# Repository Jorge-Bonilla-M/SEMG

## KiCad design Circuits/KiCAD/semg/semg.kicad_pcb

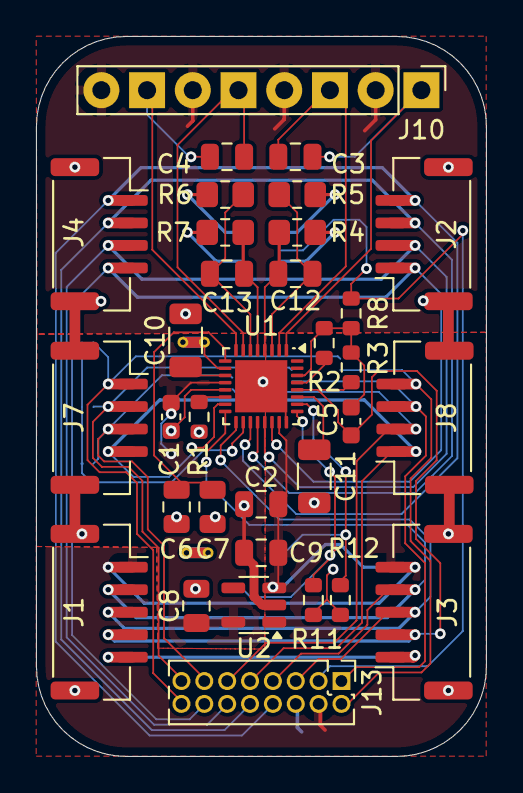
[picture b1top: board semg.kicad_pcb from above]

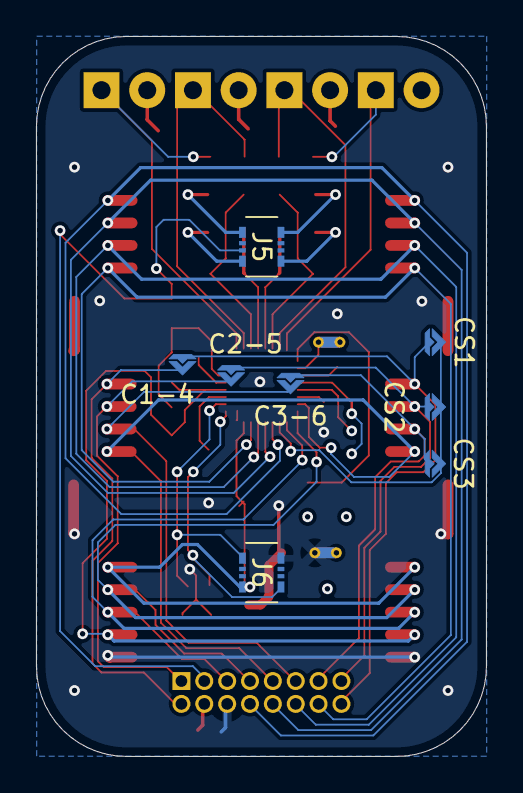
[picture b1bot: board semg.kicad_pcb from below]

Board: 4 copper layers, 25.0 x 40.0 mm, 43 parts (8 on the bottom side), 41 nets.

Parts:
C1: 100nF; C_0603_1608Metric
C1-4, C2-5, C3-6: SolderJumper_2_Open; JumperDiamond
C2, C7: 100nF; C_0805_2012Metric
C3, C4, C12, C13: 4.7nF; C_0805_2012Metric
C5: 1.5nF; C_0603_1608Metric
C6: 22uF; C_0805_2012Metric
C8, C9: 1uF; C_0805_2012Metric
C10, C11: 2.2uF; C_1206_3216Metric
CS1, CS2, CS3: SolderJumper_2_Open; JumperDiamond
J1, J3: Miscelaneous; JST_GH_SM05B-GHS-TB_1x05-1MP_P1.25mm_Horizontal
J2, J4: SPI; JST_GH_SM04B-GHS-TB_1x04-1MP_P1.25mm_Horizontal
J5, J6: 505006-0812; 5050060812
J7, J8: CS_SPI; JST_GH_SM04B-GHS-TB_1x04-1MP_P1.25mm_Horizontal
J10: Conn_01x08_Pin; PinHeader_1x08_P2.54mm_Vertical
J13: Conn_02x08_Odd_Even; PinHeader_2x08_P1.27mm_Vertical
NT1, NT2: NetTie_2; NetTie-2_THT_Pad0.3mm
R1: 1k; R_0603_1608Metric
R2, R8: 100k; R_0603_1608Metric
R3: 1M; R_0603_1608Metric
R4, R5, R6, R7: 4.7k; R_0805_2012Metric_Pad1.20x1.40mm_HandSolder
R11, R12: 10k; R_0603_1608Metric
U1: ADS1292IRSMR; QFN-32-1EP_4x4mm_P0.4mm_EP2.9x2.9mm
U2: AP2112K-3.3; SOT-23-5

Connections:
+3.3V: C2.1, C9.2, J1.1, J3.5, J6.P2, J13.4, U1.23 (DVDD), U2.1 (VIN), U2.3 (EN)
+3.3VA: C1.1, C8.2, U1.12 (AVDD), U2.5 (VOUT)
CLK: J1.3, J3.3, J13.5, U1.17 (CLK)
CS: CS1.2 (B), CS2.2 (B), CS3.2 (B), U1.18 (~CS)
CS1: C1-4.1 (A), CS1.1 (A), J7.1, J13.16
CS2: C2-5.1 (A), CS2.1 (A), J7.2, J13.15
CS3: C3-6.1 (A), CS3.1 (A), J7.3, J13.13
CS4: C1-4.2 (B), J8.4, J13.2
CS5: C2-5.2 (B), J8.3, J13.1
CS6: C3-6.2 (B), J8.2, J13.11
DRDY: J2.1, J4.4, J13.14, U1.22 (~DRDY)
GND: C2.2, C9.1, C10.2, C11.2, J1.5, J1.MP (Pin_6), J2.MP (Pin_5), J3.1, J3.MP (Pin_6), J4.MP (Pin_5), J6.P3, J7.MP (Pin_5), J8.MP (Pin_5), J13.6, NT1.1, R1.2, R11.2, R12.2, U1.24 (DGND), U1.33 (EXP), U2.2 (GND)
GNDA: C1.2, C6.2, C7.2, C8.1, J10.2, J10.4, J10.6, J10.8, NT1.2, NT2.2, U1.13 (AVSS)
GPIO1: J6.P4, R12.1, U1.26 (GPIO1/RCLK1)
GPIO2: J6.P1, R11.1, U1.25 (GPIO2/RCLK2)
IN1N: C12.2, R5.2, U1.3 (IN1N)
IN1N_: J5.P4, R5.1
IN1P: C12.1, R4.2, U1.4 (IN1P)
IN1P_: J5.P2, R4.1
IN2N: C13.2, R7.2, U1.5 (IN2N)
IN2N_: J5.P1, R7.1
IN2P: C13.1, R6.2, U1.6 (IN2P)
IN2P_: J5.P3, R6.1
MISO: J2.2, J4.3, J13.12, U1.21 (DOUT)
MOSI: J2.4, J4.1, J13.8, U1.19 (DIN)
unnamed: R1.1, U1.14 (CLKSEL)
unnamed: C10.1, U1.11 (VCAP1)
unnamed: C11.1, U1.27 (VCAP2)
PGA1N: C3.1, J10.1, U1.1 (PGA1N)
PGA1P: C3.2, J10.3, U1.2 (PGA1P)
PGA2N: C4.1, J10.5, U1.7 (PGA2N)
PGA2P: C4.2, J10.7, U1.8 (PGA2P)
PWDN: J7.4, J8.1, J13.9, U1.15 (~PWDN/RST)
RLD: J5.S2, J13.3, R8.2
RLDIN: R2.2, U1.29 (RLDIN/RLDREF)
RLDINV: C5.1, J1.4, J3.2, R3.2, U1.28 (RLDINV)
RLDOUT: C5.2, R2.1, R3.1, R8.1, U1.30 (RLDOUT)
SPICLK: J2.3, J4.2, J13.10, U1.20 (SCLK)
START: J1.2, J3.4, J13.7, U1.16 (START)
VREFN: NT2.1, U1.10 (VREFN)
VREFP: C6.1, C7.1, U1.9 (VREFP)

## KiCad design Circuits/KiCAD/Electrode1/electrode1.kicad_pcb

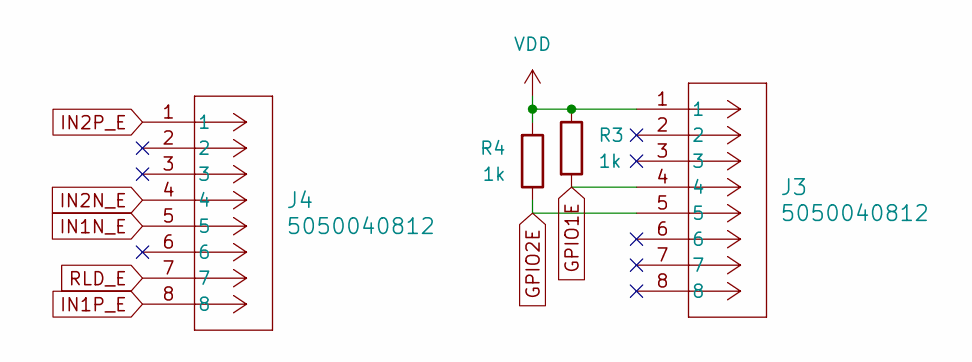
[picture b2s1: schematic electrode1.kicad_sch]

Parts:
J3, J4: 5050040812; CONN8_505004-0812_MOL
R3, R4: 1k; C_0805_2012Metric

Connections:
GPIO1E: J3.4, R3.2
GPIO2E: J3.5, R4.1
IN1N_E: J4.5
IN1P_E: J4.8
IN2N_E: J4.4
IN2P_E: J4.1
RLD_E: J4.7
VDD: J3.1, R3.1, R4.2

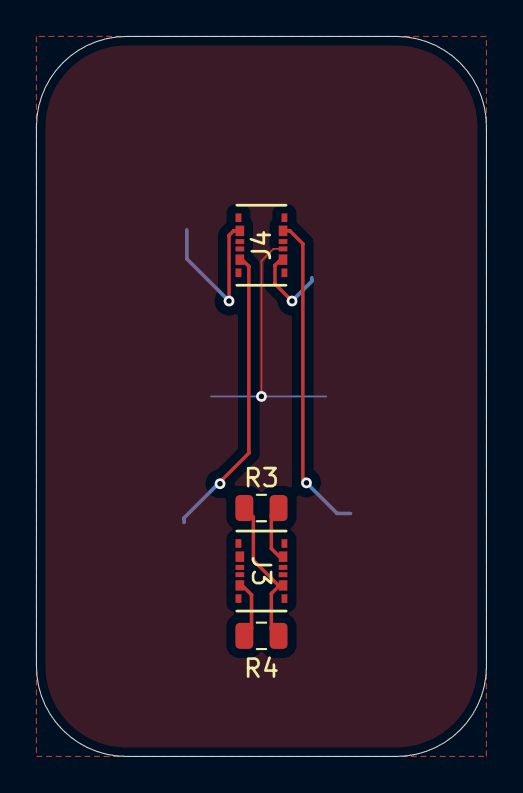
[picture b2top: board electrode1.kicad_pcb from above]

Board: 2 copper layers, 25.0 x 40.0 mm, 4 parts (0 on the bottom side), 3 nets.

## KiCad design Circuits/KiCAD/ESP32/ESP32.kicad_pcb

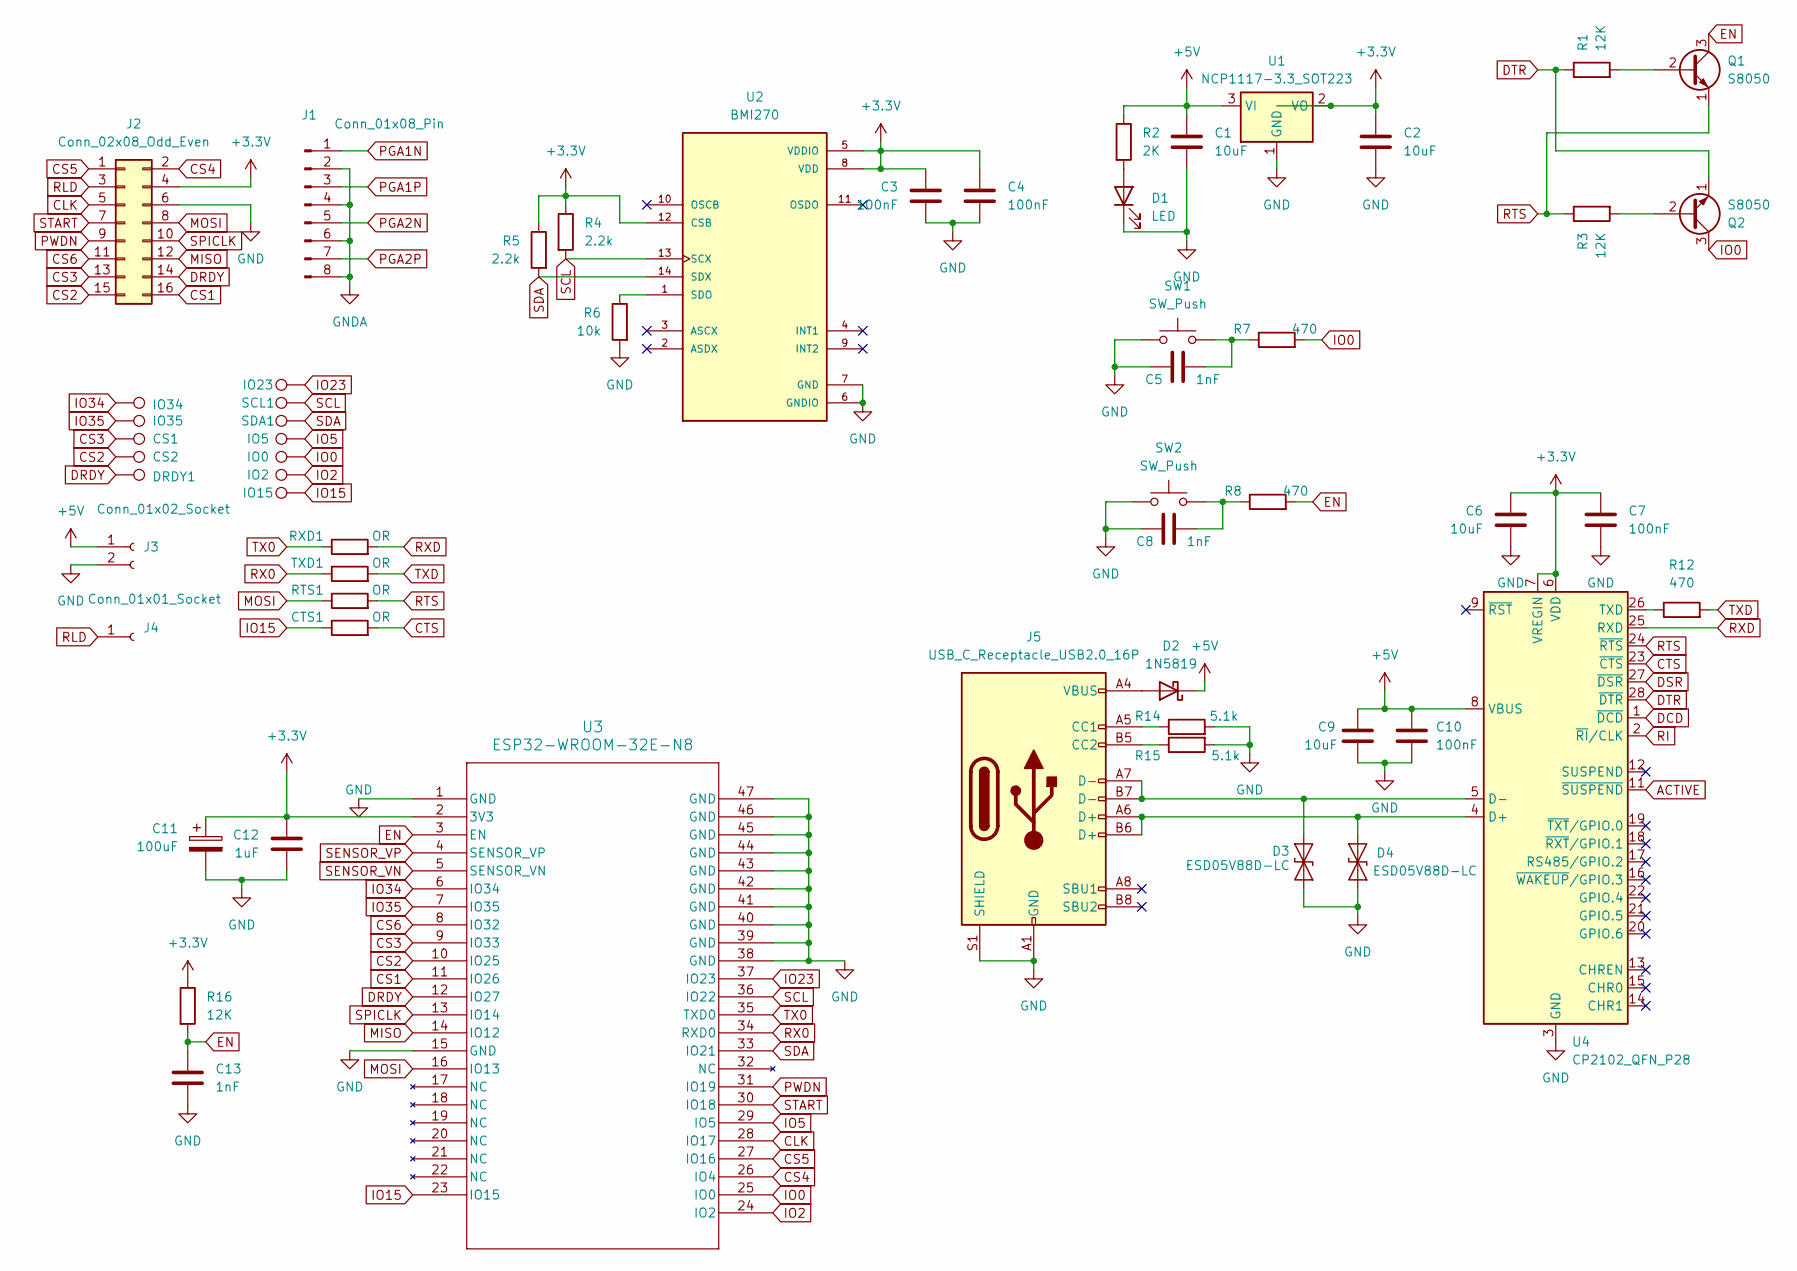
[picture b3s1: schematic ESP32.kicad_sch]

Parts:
C1, C2, C6, C9: 10uF; C_0805_2012Metric
C3, C4, C7, C10: 100nF; C_0805_2012Metric
C5, C8, C13: 1nF; C_0805_2012Metric
C11: 100uF; C_1210_3225Metric
C12: 1uF; C_0805_2012Metric
CS1, CS2: TestPoint; TestPoint_Pad_2.5x2.5mm
CTS1: OR; JumperDiamond
D1: LED; D_0805_2012Metric
D2: 1N5819; D_SOD-323
D3, D4: ESD05V88D-LC; DFN1006-2N
DRDY1: TestPoint; TestPoint_Pad_2.5x2.5mm
IO0, IO2, IO5, IO15, IO23, IO34, IO35: TestPoint; TestPoint_Pad_2.5x2.5mm
J1: Conn_01x08_Pin; PinHeader_1x08_P2.54mm_Vertical
J2: Conn_02x08_Odd_Even; PinHeader_2x08_P1.27mm_Vertical
J3: Conn_01x02_Socket; PinHeader_1x02_P2.54mm_Vertical
J4: Conn_01x01_Socket; PinHeader_1x01_P2.54mm_Vertical
J5: USB_C_Receptacle_USB2.0_16P; USB_C_Receptacle_HCTL_HC-TYPE-C-16P-01A
Q1, Q2: S8050; SOT-23
R1, R3, R16: 12K; R_0805_2012Metric
R2: 2K; R_0805_2012Metric
R4, R5: 2.2k; R_0805_2012Metric
R6: 10k; R_0805_2012Metric
R7, R8, R12: 470; R_0805_2012Metric
R14, R15: 5.1k; R_0805_2012Metric
RTS1: OR; JumperDiamond
RXD1: OR; JumperDiamond
SCL1: TestPoint; TestPoint_Pad_2.5x2.5mm
SDA1: TestPoint; TestPoint_Pad_2.5x2.5mm
SW1, SW2: SW_Push; SW_Push_1P1T_XKB_TS-1187A
TXD1: OR; JumperDiamond
U1: NCP1117-3.3_SOT223; SOT-223-3_TabPin2
U2: BMI270; XDCR_BMI270
U3: ESP32-WROOM-32E-N8; ESP32­WROOM­32E_EXP
U4: CP2102_QFN_P28; QFN-28-1EP_5x5mm_P0.5mm_EP3.35x3.35mm

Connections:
+3.3V: C2.1, C3.1, C4.1, C6.1, C7.1, C11.1, C12.1, J2.4, R4.1, R5.1, R16.1, U1.2 (VO), U2.5 (VDDIO), U2.8 (VDD), U2.12 (CSB), U3.2 (3V3), U4.6 (VDD), U4.7 (VREGIN)
+5V: C1.1, C9.1, C10.1, D2.1 (K), J3.1, R2.1, U1.3 (VI), U4.8 (VBUS)
ACTIVE: U4.11 (~SUSPEND)
CLK: J2.5, U3.28 (IO17)
CS1: J2.16, U3.11 (IO26)
CS2: CS2.1, J2.15, U3.10 (IO25)
CS3: CS1.1, J2.13, U3.9 (IO33)
CS4: J2.2, U3.26 (IO4)
CS5: J2.1, U3.27 (IO16)
CS6: J2.11, U3.8 (IO32)
CTS: CTS1.2, U4.23 (~CTS)
DCD: U4.1 (~DCD)
DRDY: DRDY1.1, J2.14, U3.12 (IO27)
DSR: U4.27 (~DSR)
DTR: Q2.1 (E), R1.1, U4.28 (~DTR)
EN: C13.1, Q1.3 (C), R8.2, R16.2, U3.3 (EN)
GND: C1.2, C2.2, C3.2, C4.2, C5.1, C6.2, C7.2, C8.1, C9.2, C10.2, C11.2, C12.2, C13.2, D1.1 (K), D3.1 (A1), D4.1 (A1), J2.6, J3.2, J5.A1 (GND), J5.A12 (GND), J5.B1 (GND), J5.B12 (GND), J5.S1 (SHIELD), R6.2, R14.2, R15.2, SW1.1, SW2.1, U1.1 (GND), U2.6 (GNDIO), U2.7 (GND), U3.1 (GND), U3.15 (GND), U3.38 (GND), U3.39 (GND), U3.40 (GND), U3.41 (GND), U3.42 (GND), U3.43 (GND), U3.44 (GND), U3.45 (GND), U3.46 (GND), U3.47 (GND), U4.3 (GND), U4.29 (GND)
GNDA: J1.2, J1.4, J1.6, J1.8
IO0: IO0.1, Q2.3 (C), R7.2, U3.25 (IO0)
IO2: IO2.1, U3.24 (IO2)
IO5: IO5.1, U3.29 (IO5)
IO15: CTS1.1, IO15.1, U3.23 (IO15)
IO23: IO23.1, U3.37 (IO23)
IO34: IO34.1, U3.6 (IO34)
IO35: IO35.1, U3.7 (IO35)
MISO: J2.12, U3.14 (IO12)
MOSI: J2.8, RTS1.1, U3.16 (IO13)
unnamed: C5.2, R7.1, SW1.2
unnamed: C8.2, R8.1, SW2.2
unnamed: D1.2 (A), R2.2
unnamed: D2.2 (A), J5.A4 (VBUS), J5.A9 (VBUS), J5.B4 (VBUS), J5.B9 (VBUS)
unnamed: D3.2 (A2), J5.A7 (D-), J5.B7 (D-), U4.5 (D-)
unnamed: D4.2 (A2), J5.A6 (D+), J5.B6 (D+), U4.4 (D+)
unnamed: J5.A5 (CC1), R14.1
unnamed: J5.B5 (CC2), R15.1
unnamed: Q1.2 (B), R1.2
unnamed: Q2.2 (B), R3.2
unnamed: R6.1, U2.1 (SDO)
unnamed: R12.1, U4.26 (TXD)
PGA1N: J1.1
PGA1P: J1.3
PGA2N: J1.5
PGA2P: J1.7
PWDN: J2.9, U3.31 (IO19)
RI: U4.2 (~RI/CLK)
RLD: J2.3, J4.1
RTS: Q1.1 (E), R3.1, RTS1.2, U4.24 (~RTS)
RX0: TXD1.1, U3.34 (RXD0)
RXD: RXD1.2, U4.25 (RXD)
SCL: R4.2, SCL1.1, U2.13 (SCX), U3.36 (IO22)
SDA: R5.2, SDA1.1, U2.14 (SDX), U3.33 (IO21)
SENSOR_VN: U3.5 (SENSOR_VN)
SENSOR_VP: U3.4 (SENSOR_VP)
SPICLK: J2.10, U3.13 (IO14)
START: J2.7, U3.30 (IO18)
TX0: RXD1.1, U3.35 (TXD0)
TXD: R12.2, TXD1.2

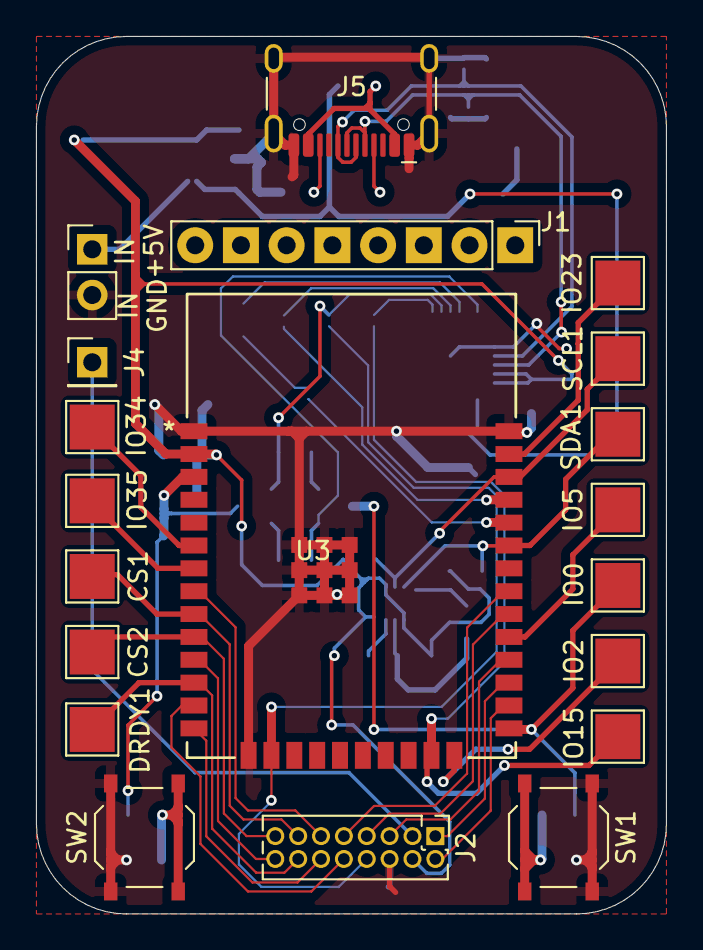
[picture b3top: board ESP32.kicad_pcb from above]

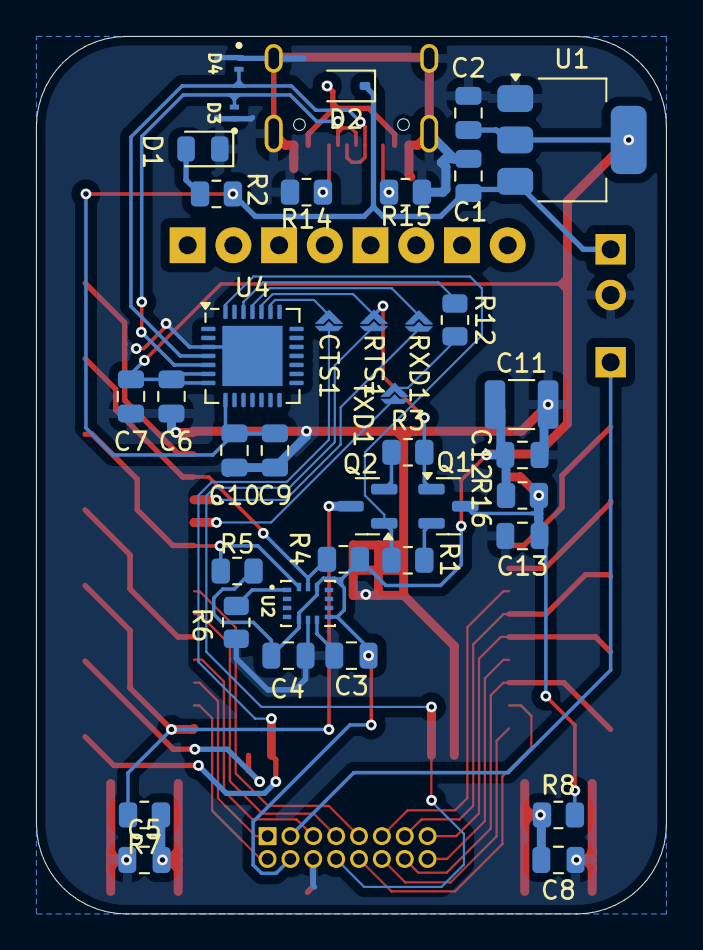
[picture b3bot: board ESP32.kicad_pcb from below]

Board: 2 copper layers, 35.0 x 48.8 mm, 58 parts (38 on the bottom side), 47 nets.

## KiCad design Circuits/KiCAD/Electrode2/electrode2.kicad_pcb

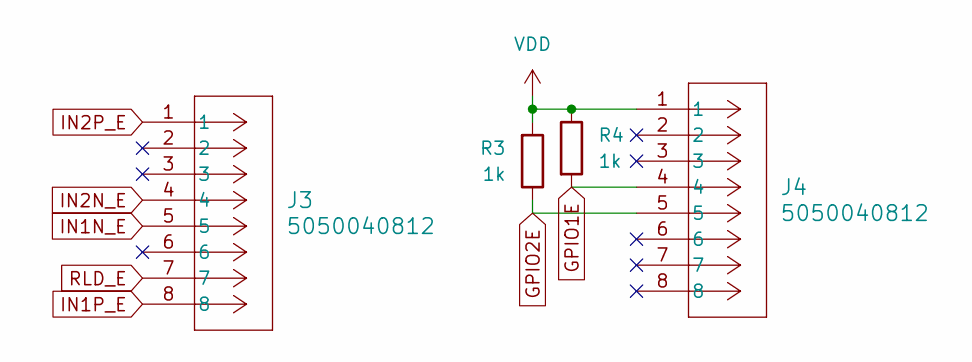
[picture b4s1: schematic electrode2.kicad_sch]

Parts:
J3, J4: 5050040812; CONN8_505004-0812_MOL
R3, R4: 1k; C_0805_2012Metric

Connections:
GPIO1E: J4.4, R4.2
GPIO2E: J4.5, R3.1
IN1N_E: J3.5
IN1P_E: J3.8
IN2N_E: J3.4
IN2P_E: J3.1
RLD_E: J3.7
VDD: J4.1, R3.2, R4.1

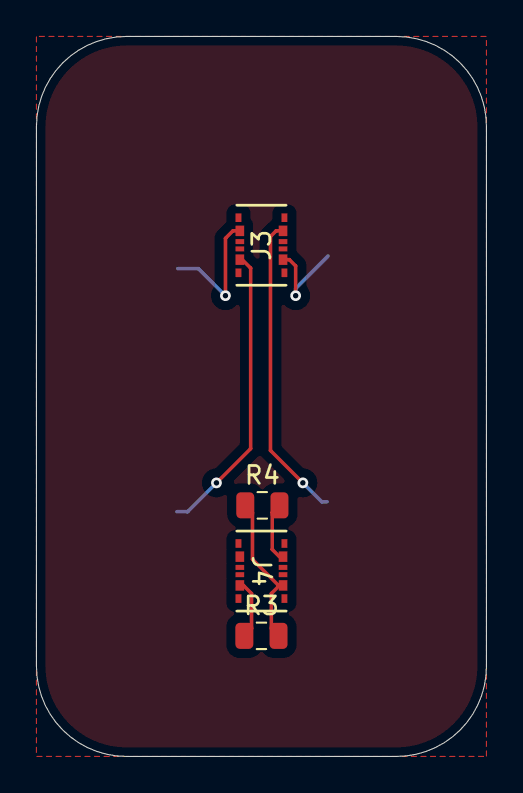
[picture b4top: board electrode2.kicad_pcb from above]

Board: 2 copper layers, 25.0 x 40.0 mm, 4 parts (0 on the bottom side), 3 nets.

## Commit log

2024-11-18 Carpetas principales, circuitos finales, modelos 3d, codigo sin terminar
2024-11-26 Final 3D models, test GUI with exe
2024-11-26 Arduino Code
2024-11-26 Requirements for Python Script
2024-11-26 Requirements for Python Test GUI
